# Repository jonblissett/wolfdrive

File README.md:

# wolfdrive
Motor drive inverter designed to be used with the Cree CAS325M12HM2 silicon carbide MOSFETs.

Anticipated specifications:
Peak power, 250kW
Current, ~300Arms
DC bus voltage, <800Vdc

## /controller

Control board, using STM32H743 microcontroller. Accepts analogue signals for throttle, will output FOC signals to gate drivers.

## /firmware

Software repository for controller - currently empty!

## /DCbus

PCB to connect DC bus capacitors with low stray inductance

## /DCsnubber

Alternative DC bus capacitor connection for small capacitors above devices like in early evaluation kit from Cree. May work out to be a cheaper option than /DCbus.

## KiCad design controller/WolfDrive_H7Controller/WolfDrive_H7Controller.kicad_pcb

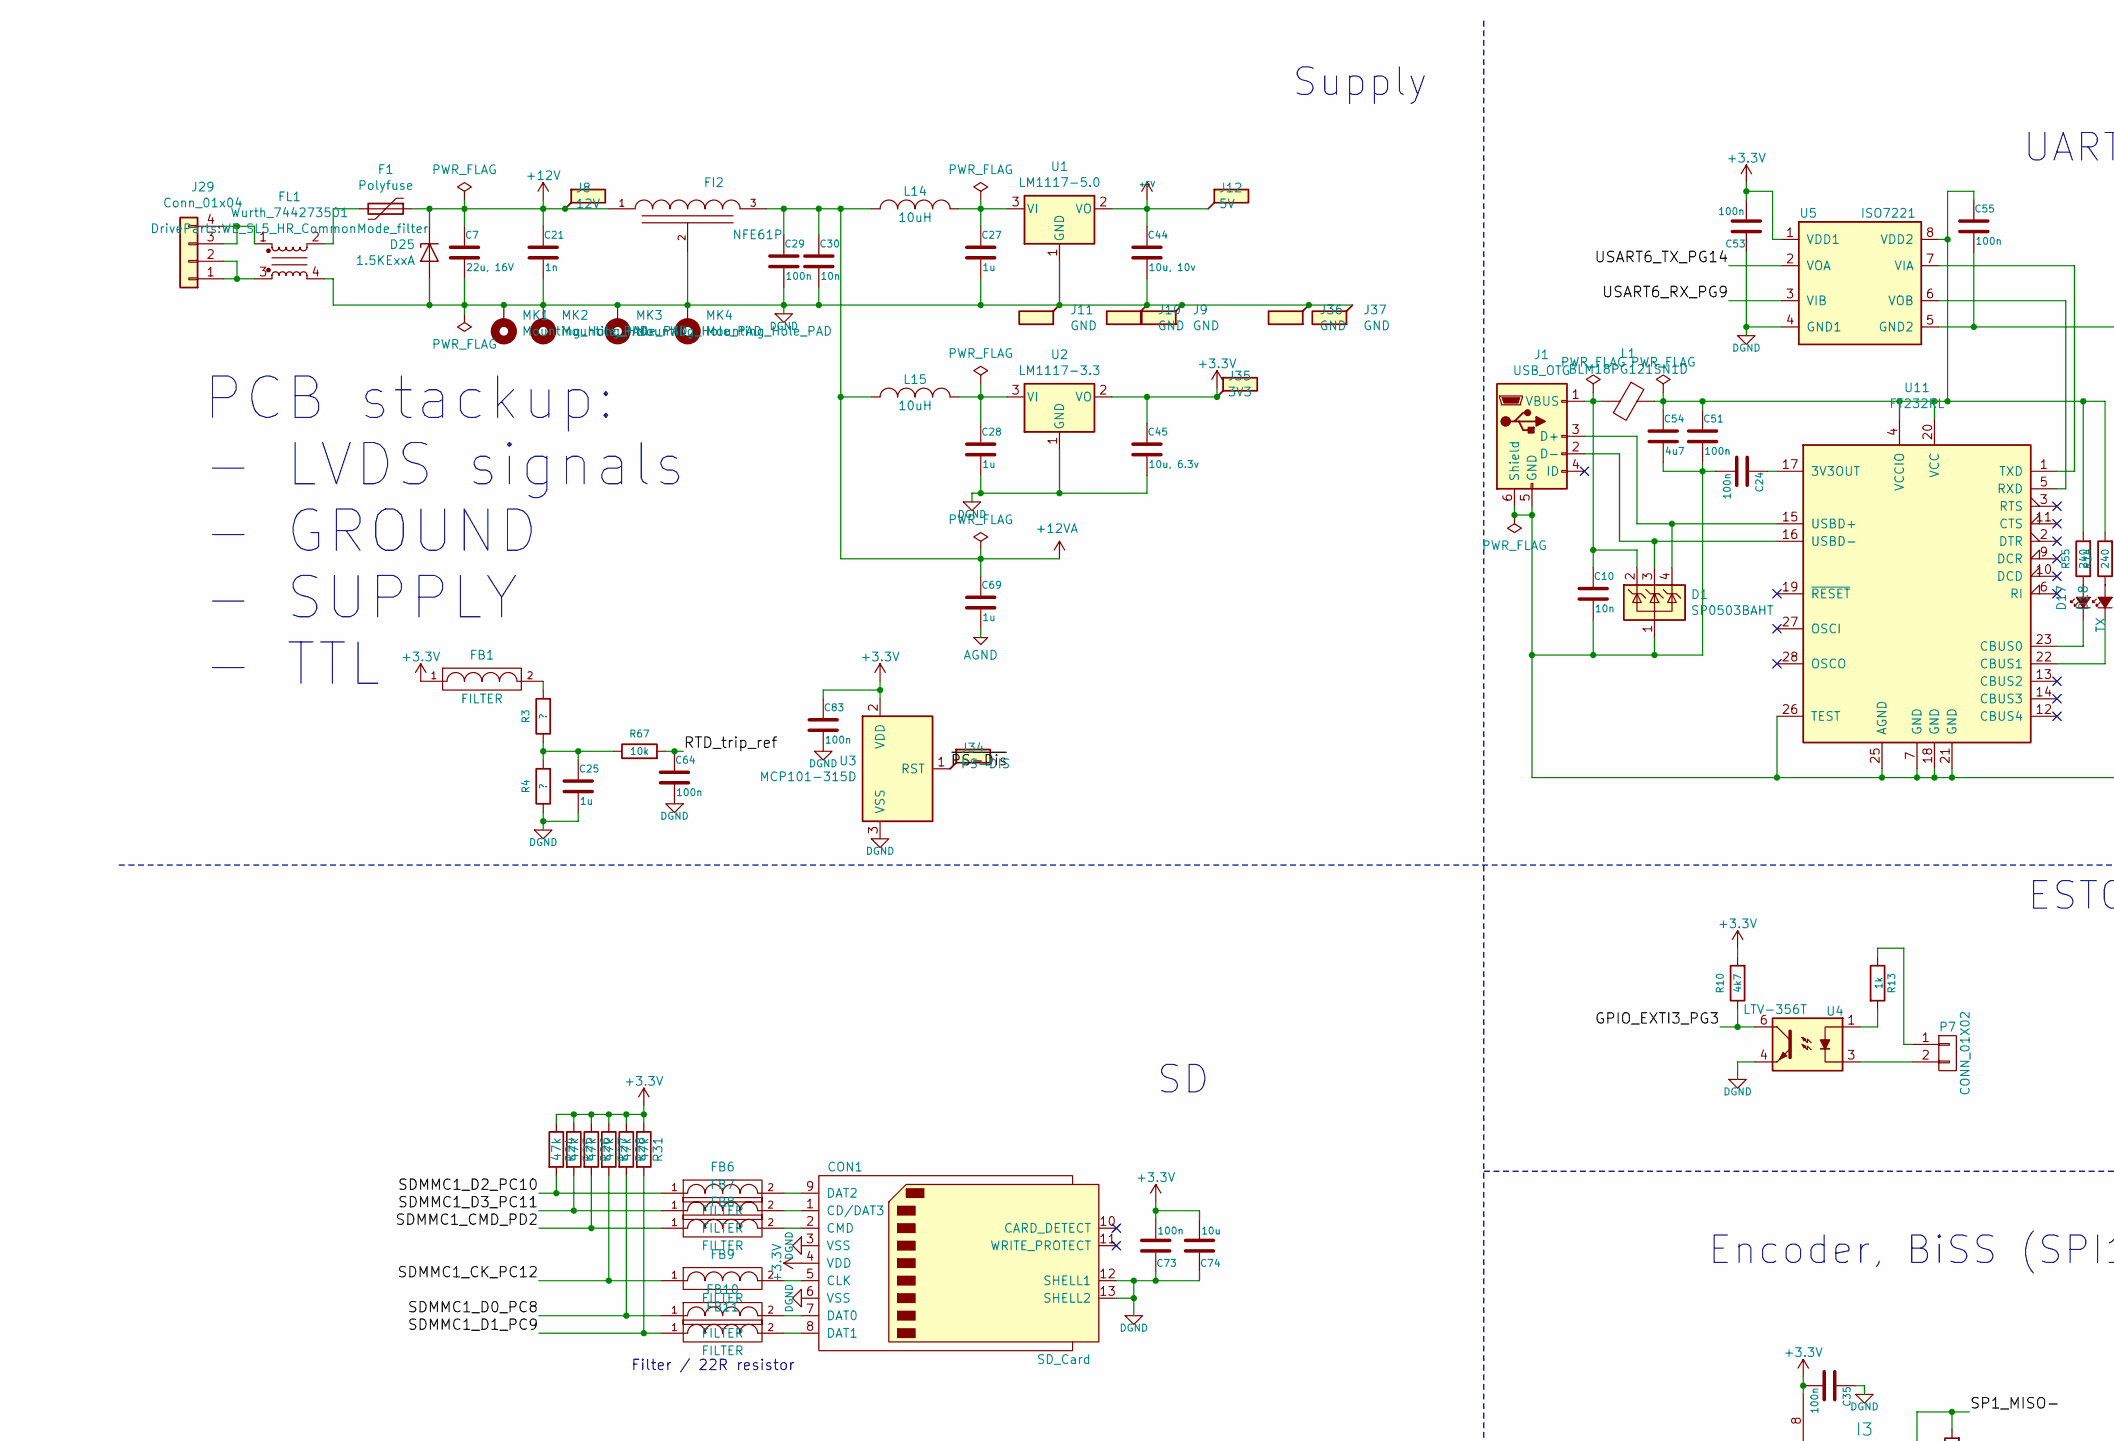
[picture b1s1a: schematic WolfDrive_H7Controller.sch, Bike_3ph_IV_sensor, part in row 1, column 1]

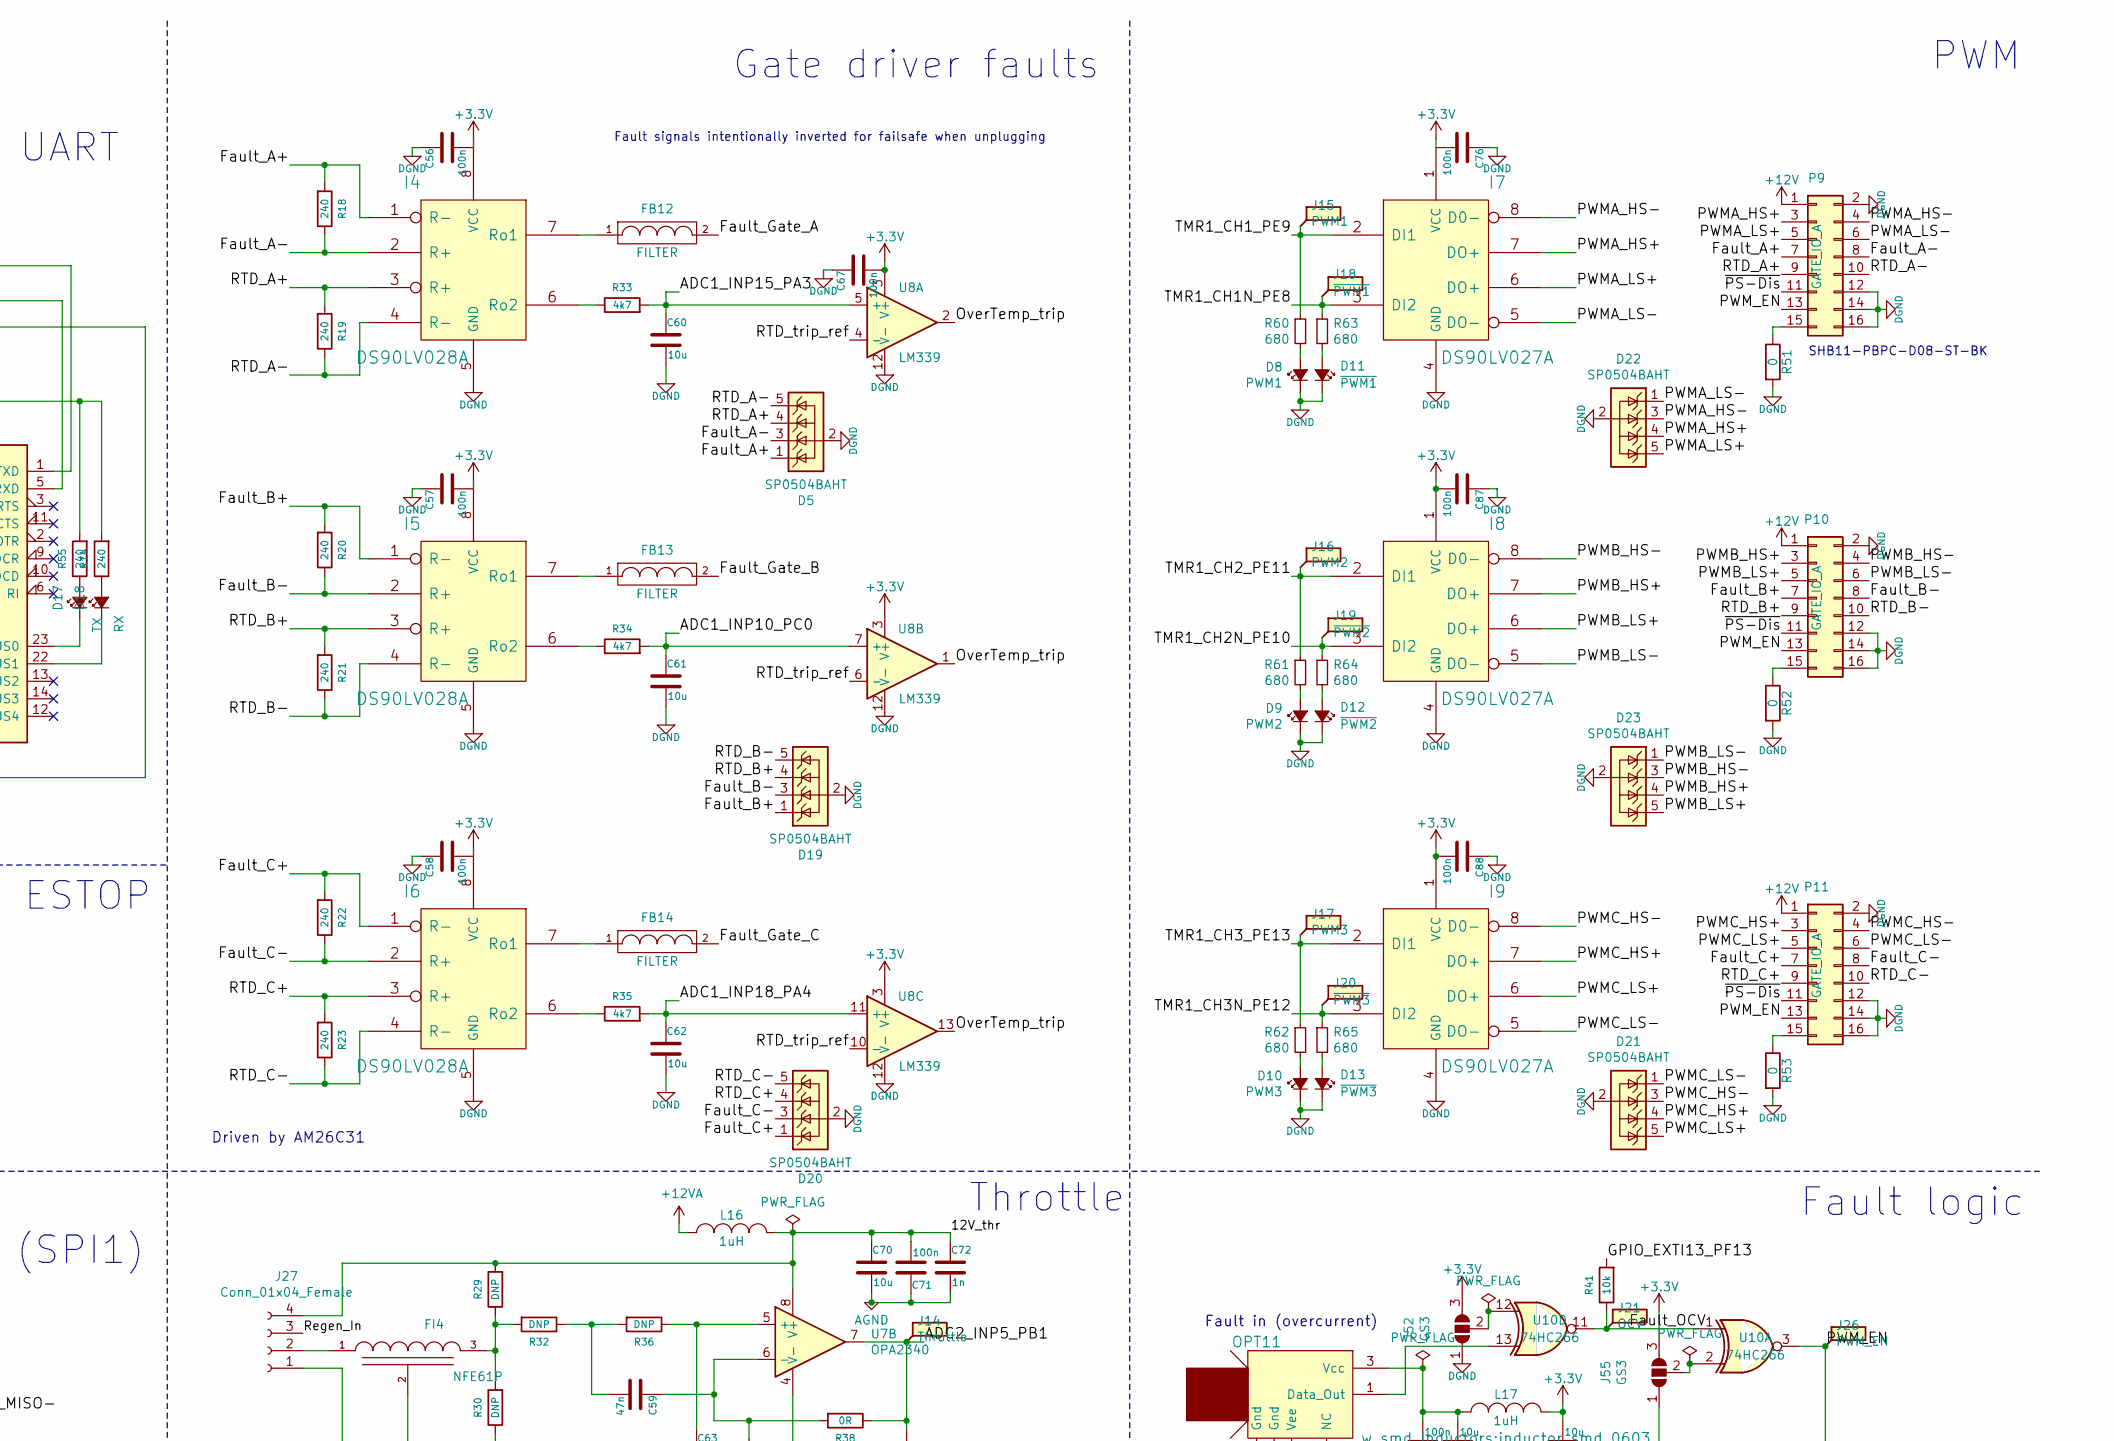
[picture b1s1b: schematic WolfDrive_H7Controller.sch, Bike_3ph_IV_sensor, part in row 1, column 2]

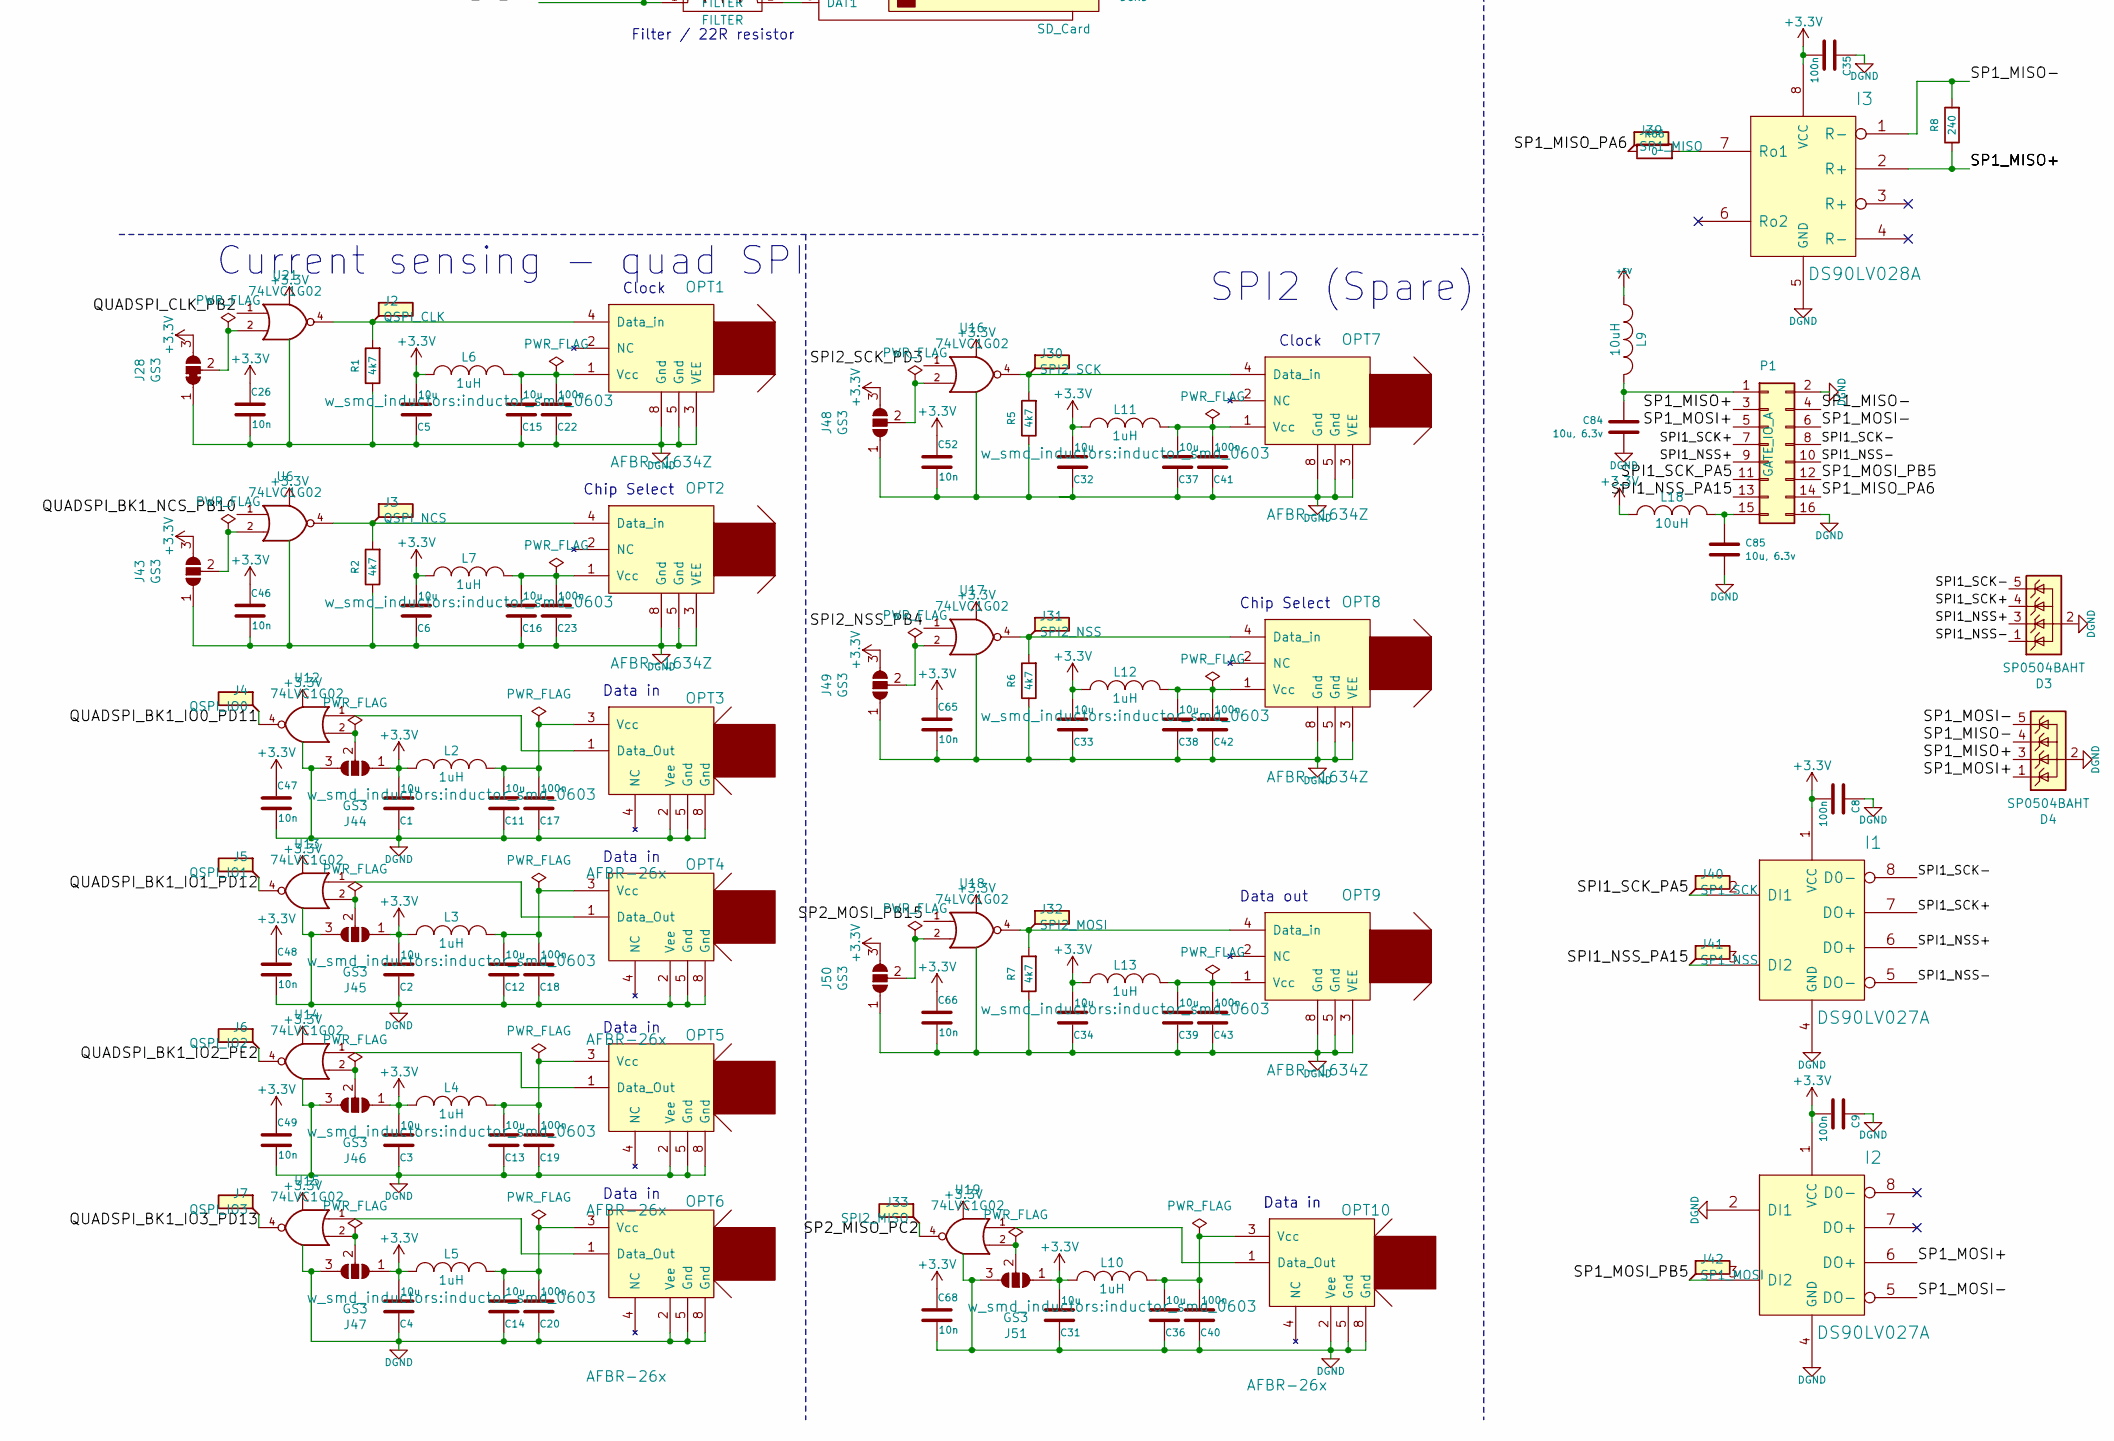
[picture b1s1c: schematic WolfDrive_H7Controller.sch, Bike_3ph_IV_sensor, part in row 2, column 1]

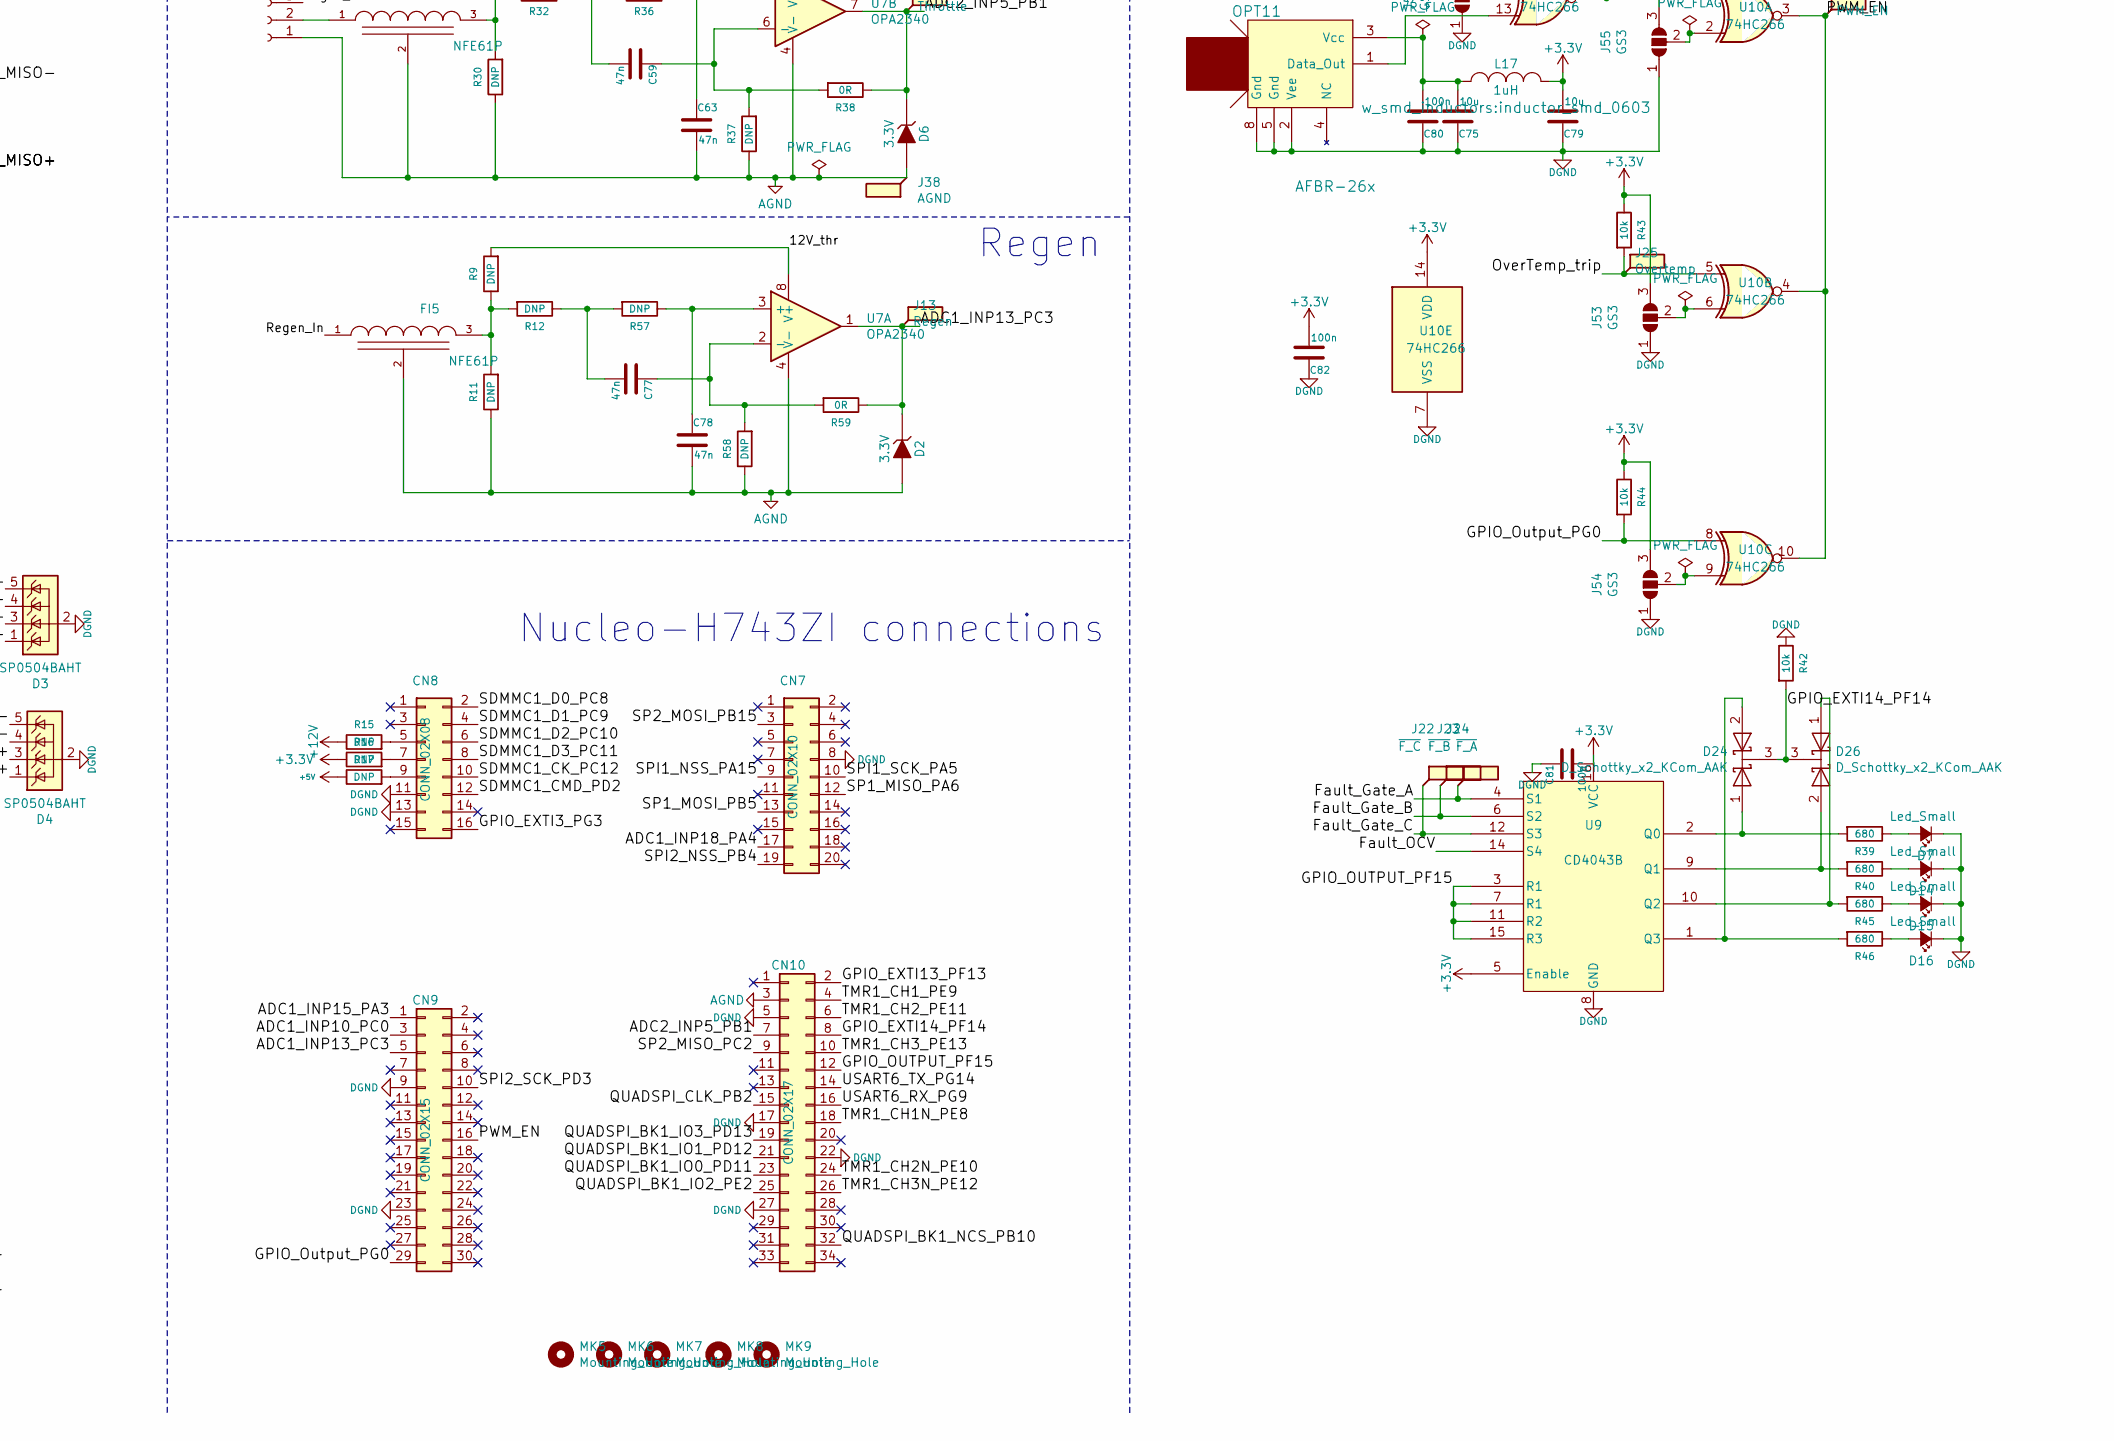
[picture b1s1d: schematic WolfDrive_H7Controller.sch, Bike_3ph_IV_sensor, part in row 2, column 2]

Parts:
C1, C2, C3, C4, C5, C6, C11, C12, C13, C14, C15, C16, C31, C32, C33, C34, C36, C37, C38, C39, C60, C61, C62, C70, C74, C75, C79: 10u; C_0805
C7: 22u, 16V; C_1210_HandSoldering
C8, C9, C17, C18, C19, C20, C22, C23, C24, C29, C35, C40, C41, C42, C43, C51, C53, C55, C56, C57, C58, C64, C67, C71, C73, C76, C80, C81, C82, C83, C87, C88: 100n; C_0603_HandSoldering
C10, C26, C30, C46, C47, C48, C49, C52, C65, C66, C68: 10n; C_0603_HandSoldering
C21, C72: 1n; C_0603_HandSoldering
C25, C27, C28, C69: 1u; C_0603_HandSoldering
C44: 10u, 10v; C_0805
C45, C84, C85: 10u, 6.3v; C_0805
C54: 4u7; C_0805
C59, C63, C77, C78: 47n; C_0603_HandSoldering
CN7: CONN_02X10; Socket_Strip_Straight_2x10_Pitch2.54mm
CN8: CONN_02X08; Socket_Strip_Straight_2x08_Pitch2.54mm
CN9: CONN_02X15; Socket_Strip_Straight_2x15_Pitch2.54mm
CN10: CONN_02X17; Socket_Strip_Straight_2x17_Pitch2.54mm
CON1: SD_Card; SD_Card_Receptacle
D1: SP0503BAHT; SOT-143R_Reverse_Handsoldering
D2, D6: 3.3V; D_SOD-523
D3, D4, D5, D19, D20, D21, D22, D23: SP0504BAHT; TSOT-23-5
D7, D14, D15, D16: Led_Small; LED_0603_HandSoldering
D8: PWM1; LED_0603_HandSoldering
D9: PWM2; LED_0603_HandSoldering
D10: PWM3; LED_0603_HandSoldering
D11: ~PWM1; LED_0603_HandSoldering
D12: ~PWM2; LED_0603_HandSoldering
D13: ~PWM3; LED_0603_HandSoldering
D17: TX; LED_0603_HandSoldering
D18: RX; LED_0603_HandSoldering
D24, D26: D_Schottky_x2_KCom_AAK; TSOT-23
D25: 1.5KExxA; D_SMB-SMC_Universal_Handsoldering
F1: Polyfuse; Fuse_1812_4532Metric_Pad1.24x3.50mm_HandSolder
FB1, FB6, FB7, FB8, FB9, FB10, FB11, FB12, FB13, FB14: FILTER; inductor_smd_0805
FI2, FI4, FI5: NFE61P; EMI_Filter_murata
FL1: Wurth_744273501; WE_SL5_HR_CommonMode_filter
I1, I2, I7, I8, I9: DS90LV027A; SOIC-8_3.9x4.9mm_Pitch1.27mm
I3, I4, I5, I6: DS90LV028A; SOIC-8_3.9x4.9mm_Pitch1.27mm
J1: USB_OTG; USB_Mini-B
J2: QSPI_CLK; Test_Point
J3: QSPI_NCS; Test_Point
J4: QSPI_IO0; Test_Point
J5: QSPI_IO1; Test_Point
J6: QSPI_IO2; Test_Point
J7: QSPI_IO3; Test_Point
J8: 12V; Test_Point
J9, J10, J11, J36, J37: GND; Test_Point
J12: 5V; Test_Point
J13: Regen; Test_Point
J14: Throttle; Test_Point
J15: PWM1; Test_Point
J16: PWM2; Test_Point
J17: PWM3; Test_Point
J18: ~PWM1; Test_Point
J19: ~PWM2; Test_Point
J20: ~PWM3; Test_Point
J21: OCV; Test_Point
J22: ~F_C; Test_Point
J23: ~F_B; Test_Point
J24: ~F_A; Test_Point
J25: Overtemp; Test_Point
J26: PWM_EN; Test_Point
J27: Conn_01x04_Female; TerminalBlock_Pheonix_PT-3.5mm_4pol
J28, J43, J44, J45, J46, J47, J48, J49, J50, J51, J52, J53, J54, J55: GS3
J29: Conn_01x04; PhoenixContact_MSTB-GF_04x5.08mm_Angled_ThreadedFlange_Moun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
J30: SPI2_SCK; Test_Point
J31: SPI2_NSS; Test_Point
J32: SPI2_MOSI; Test_Point
J33: SPI2_MISO; Test_Point
J34: PS-DIS; Test_Point
J35: 3V3; Test_Point
J38: AGND; Test_Point
J39: SP1_MISO; Test_Point
J40: SP1_SCK; Test_Point
J41: SP1_NSS; Test_Point
J42: SP1_MOSI; Test_Point
L1: BLM18PG121SN1D; inductor_smd_0603
L2, L3, L4, L5, L6, L7, L10, L11, L12, L13, L16, L17: 1uH; inductor_smd_0603
L9, L14, L15, L18: 10uH; Neosid_Inductor_SM-NE45_SMD1812
MK1, MK2, MK3, MK4: Mounting_Hole_PAD; MountingHole_4.3mm_M4_Pad_Via
MK5, MK6, MK7, MK8, MK9: Mounting_Hole; MountingHole_3.2mm_M3
OPT1, OPT2, OPT7, OPT8, OPT9: AFBR-1634Z; HFBR-xx2xZ
OPT3, OPT4, OPT5, OPT6, OPT10, OPT11: AFBR-26x; HFBR-xx2xZ
P1, P9, P10, P11: GATE_IO_A; IDC-Header_2x08_Pitch2.54mm_Straight
P7: CONN_01X02; TerminalBlock_Pheonix_PT-3.5mm_2pol
R1, R2, R5, R6, R7, R10, R33, R34, R35: 4k7; R_0603_HandSoldering
R3, R4: ?; R_0603_HandSoldering
R8, R14, R18, R19, R20, R21, R22, R23, R55: 240; R_0603_HandSoldering
R9, R11, R12, R15, R16, R17, R29, R30, R32, R36, R37, R57, R58: DNP; R_0603_HandSoldering
R13: 1k; R_0603_HandSoldering
R24, R25, R26, R27, R28, R31: 47k; R_0603_HandSoldering
R38, R59: 0R; R_0603_HandSoldering
R39, R40, R45, R46, R60, R61, R62, R63, R64, R65: 680; R_0603_HandSoldering
R41, R42, R43, R44, R67: 10k; R_0603_HandSoldering
R51, R52, R53, R66: 0; R_0603_HandSoldering
U1: LM1117-5.0; TO-263-3_TabPin2
U2: LM1117-3.3; TO-263-3_TabPin2
U3: MCP101-315D; SOT-23_Handsoldering
U4: LTV-356T; DIP-6_W7.62mm_SMD
U5: ISO7221; SOIC-8_3.9x4.9mm_Pitch1.27mm
U6, U12, U13, U14, U15, U16, U17, U18, U19, U21: 74LVC1G02; SOT-353_SC-70-5_Handsoldering
U7: OPA2340; SOIC-8_3.9x4.9mm_Pitch1.27mm
U8: LM339; SOIC-14_3.9x8.7mm_Pitch1.27mm
U9: CD4043B; SOIC-16_3.9x9.9mm_Pitch1.27mm
U10: 74HC266; SOIC-14_3.9x8.7mm_Pitch1.27mm
U11: FT232RL; SSOP-28_5.3x10.2mm_Pitch0.65mm

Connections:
+3V3: C1.2, C2.2, C3.2, C4.2, C5.2, C6.2, C8.2, C9.2, C26.1, C31.2, C32.2, C33.2, C34.2, C35.2, C45.1, C46.1, C47.1, C48.1, C49.1, C52.1, C53.2, C56.2, C57.2, C58.2, C65.1, C66.1, C67.2, C68.1, C73.2, C74.2, C76.2, C79.2, C81.2, C82.2, C83.1, C87.2, C88.2, CON1.4 (VDD), FB1.1, I1.1 (VCC), I2.1 (VCC), I3.8 (VCC), I4.8 (VCC), I5.8 (VCC), I6.8 (VCC), I7.1 (VCC), I8.1 (VCC), I9.1 (VCC), J28.3 (B), J35.1, J43.3 (B), J44.1 (A), J45.1 (A), J46.1 (A), J47.1 (A), J48.3 (B), J49.3 (B), J50.3 (B), J51.1 (A), J52.3 (B), J53.3 (B), J54.3 (B), J55.3 (B), L2.2, L3.2, L4.2, L5.2, L6.2, L7.2, L10.2, L11.2, L12.2, L13.2, L17.1, L18.2, R10.2, R16.1, R24.1, R25.1, R26.1, R27.1, R28.1, R31.1, R43.1, R44.1, U2.2 (VO), U3.2 (VDD), U5.1 (VDD1), U6.5 (VCC), U8.3 (V+), U9.5 (Enable), U9.16 (VCC), U10.14 (VDD), U12.5 (VCC), U13.5 (VCC), U14.5 (VCC), U15.5 (VCC), U16.5 (VCC), U17.5 (VCC), U18.5 (VCC), U19.5 (VCC), U21.5 (VCC)
+5V: C44.1, J12.1, L9.1, R17.1, U1.2 (VO)
+12V: C7.1, C21.1, D25.1 (A1), F1.1, FI2.1 (VI), J8.1, P9.1, P10.1, P11.1, R15.1
+12VA: C29.1, C30.1, C69.1, FI2.3 (VO), L14.1, L15.1, L16.2
/12V_thr: C70.1, C71.2, C72.1, J27.4, L16.1, R9.2, R29.2, U7.8 (V+)
/ADC1_INP10_PC0: C61.1, CN9.3, R34.2, U8.7 (+)
/ADC1_INP13_PC3: CN9.5, D2.1 (K), J13.1, R59.1, U7.1
/ADC1_INP15_PA3: C60.1, CN9.1, R33.2, U8.5 (+)
/ADC1_INP18_PA4: C62.1, CN7.17, R35.2, U8.11 (+)
/ADC2_INP5_PB1: CN10.7, D6.1 (K), J14.1, R38.1, U7.7
/Fault_A+: D5.1 (K), I4.1 (R-), P9.7, R18.2
/Fault_A-: D5.3 (K), I4.2 (R+), P9.8, R18.1
/Fault_B+: D19.1 (K), I5.1 (R-), P10.7, R20.2
/Fault_B-: D19.3 (K), I5.2 (R+), P10.8, R20.1
/Fault_C+: D20.1 (K), I6.1 (R-), P11.7, R22.2
/Fault_C-: D20.3 (K), I6.2 (R+), P11.8, R22.1
/Fault_Gate_A: FB12.2, J24.1, U9.4 (S1)
/Fault_Gate_B: FB13.2, J23.1, U9.6 (S2)
/Fault_Gate_C: FB14.2, J22.1, U9.12 (S3)
/Fault_OCV: J21.1, R41.1, U9.14 (S4), U10.1, U10.11
/GPIO_EXTI3_PG3: CN8.16, R10.1, U4.6
/GPIO_EXTI13_PF13: CN10.2, R41.2
/GPIO_EXTI14_PF14: CN10.8, D24.3 (K), D26.3 (K), R42.2
/GPIO_OUTPUT_PF15: CN10.12, U9.3 (R1), U9.7 (R1), U9.11 (R2), U9.15 (R3)
/GPIO_Output_PG0: CN9.29, R44.2, U10.8
/OverTemp_trip: J25.1, R43.2, U8.1, U8.2, U8.13, U10.5
/PWMA_HS+: D22.4 (K), I7.7 (DO+), P9.3
/PWMA_HS-: D22.3 (K), I7.8 (D0-), P9.4
/PWMA_LS+: D22.5 (K), I7.6 (DO+), P9.5
/PWMA_LS-: D22.1 (K), I7.5 (DO-), P9.6
/PWMB_HS+: D23.4 (K), I8.7 (DO+), P10.3
/PWMB_HS-: D23.3 (K), I8.8 (D0-), P10.4
/PWMB_LS+: D23.5 (K), I8.6 (DO+), P10.5
/PWMB_LS-: D23.1 (K), I8.5 (DO-), P10.6
/PWMC_HS+: D21.4 (K), I9.7 (DO+), P11.3
/PWMC_HS-: D21.3 (K), I9.8 (D0-), P11.4
/PWMC_LS+: D21.5 (K), I9.6 (DO+), P11.5
/PWMC_LS-: D21.1 (K), I9.5 (DO-), P11.6
/PWM_EN: CN9.16, J26.1, P9.13, P10.13, P11.13, U10.3, U10.4, U10.10
/QUADSPI_BK1_IO0_PD11: CN10.23, J4.1, U12.4
/QUADSPI_BK1_IO1_PD12: CN10.21, J5.1, U13.4
/QUADSPI_BK1_IO2_PE2: CN10.25, J6.1, U14.4
/QUADSPI_BK1_IO3_PD13: CN10.19, J7.1, U15.4
/QUADSPI_BK1_NCS_PB10: CN10.32, U6.1
/QUADSPI_CLK_PB2: CN10.15, U21.1
/RTD_A+: D5.4 (K), I4.3 (R+), P9.9, R19.2
/RTD_A-: D5.5 (K), I4.4 (R-), P9.10, R19.1
/RTD_B+: D19.4 (K), I5.3 (R+), P10.9, R21.2
/RTD_B-: D19.5 (K), I5.4 (R-), P10.10, R21.1
/RTD_C+: D20.4 (K), I6.3 (R+), P11.9, R23.2
/RTD_C-: D20.5 (K), I6.4 (R-), P11.10, R23.1
/RTD_trip_ref: C64.1, R67.2, U8.4 (-), U8.6 (-), U8.10 (-)
/Regen_In: FI5.1 (VI), J27.3
/SDMMC1_CK_PC12: CN8.10, FB9.1, R27.2
/SDMMC1_CMD_PD2: CN8.12, FB8.1, R26.2
/SDMMC1_D0_PC8: CN8.2, FB10.1, R28.2
/SDMMC1_D1_PC9: CN8.4, FB11.1, R31.2
/SDMMC1_D2_PC10: CN8.6, FB6.1, R24.2
/SDMMC1_D3_PC11: CN8.8, FB7.1, R25.2
/SP1_MISO+: D4.3 (K), I3.2 (R+), P1.3, R8.1
/SP1_MISO-: D4.4 (K), I3.1 (R-), P1.4, R8.2
/SP1_MISO_PA6: CN7.12, J39.1, P1.14, R66.1
/SP1_MOSI+: D4.1 (K), I2.6 (DO+), P1.5
/SP1_MOSI-: D4.5 (K), I2.5 (DO-), P1.6
/SP1_MOSI_PB5: CN7.13, I2.3 (DI2), J42.1, P1.12
/SP2_MISO_PC2: CN10.9, J33.1, U19.4
/SP2_MOSI_PB15: CN7.3, U18.1
/SPI1_NSS+: D3.3 (K), I1.6 (DO+), P1.9
/SPI1_NSS-: D3.1 (K), I1.5 (DO-), P1.10
/SPI1_NSS_PA15: CN7.9, I1.3 (DI2), J41.1, P1.13
/SPI1_SCK+: D3.4 (K), I1.7 (DO+), P1.7
/SPI1_SCK-: D3.5 (K), I1.8 (D0-), P1.8
/SPI1_SCK_PA5: CN7.10, I1.2 (DI1), J40.1, P1.11
/SPI2_NSS_PB4: CN7.19, U17.1
/SPI2_SCK_PD3: CN9.10, U16.1
/TMR1_CH1N_PE8: CN10.18, I7.3 (DI2), J18.1, R63.1
/TMR1_CH1_PE9: CN10.4, I7.2 (DI1), J15.1, R60.1
/TMR1_CH2N_PE10: CN10.24, I8.3 (DI2), J19.1, R64.1
/TMR1_CH2_PE11: CN10.6, I8.2 (DI1), J16.1, R61.1
/TMR1_CH3N_PE12: CN10.26, I9.3 (DI2), J20.1, R65.1
/TMR1_CH3_PE13: CN10.10, I9.2 (DI1), J17.1, R62.1
/USART6_RX_PG9: CN10.16, U5.3 (VIB)
/USART6_TX_PG14: CN10.14, U5.2 (VOA)
/~PS-Dis: J34.1, P9.11, P10.11, P11.11, U3.1 (RST)
AGND: C63.2, C69.2, C70.2, C71.1, C72.2, C78.2, CN10.3, D2.2 (A), D6.2 (A), FI4.2 (GND), FI5.2 (GND), J27.1, J38.1, R11.1, R30.1, R37.1, R58.1, U7.4 (V-)
DGND: C1.1, C2.1, C3.1, C4.1, C5.1, C6.1, C7.2, C8.1, C9.1, C11.1, C12.1, C13.1, C14.1, C15.1, C16.1, C17.1, C18.1, C19.1, C20.1, C21.2, C22.1, C23.1, C25.2, C26.2, C27.2, C28.2, C29.2, C30.2, C31.1, C32.1, C33.1, C34.1, C35.1, C36.1, C37.1, C38.1, C39.1, C40.1, C41.1, C42.1, C43.1, C44.2, C45.2, C46.2, C47.2, C48.2, C49.2, C52.2, C53.1, C56.1, C57.1, C58.1, C60.2, C61.2, C62.2, C64.2, C65.2, C66.2, C67.1, C68.2, C73.1, C74.1, C75.1, C76.1, C79.1, C80.1, C81.1, C82.1, C83.2, C84.2, C85.2, C87.1, C88.1, CN7.8, CN8.11, CN8.13, CN9.9, CN9.23, CN10.5, CN10.17, CN10.22, CN10.27, CON1.3 (VSS), CON1.6 (VSS), CON1.12 (SHELL1), CON1.13 (SHELL2), D3.2 (A), D4.2 (A), D5.2 (A), D7.1 (K), D8.1 (K), D9.1 (K), D10.1 (K), D11.1 (K), D12.1 (K), D13.1 (K), D14.1 (K), D15.1 (K), D16.1 (K), D19.2 (A), D20.2 (A), D21.2 (A), D22.2 (A), D23.2 (A), D25.2 (A2), FI2.2 (GND), FL1.4, I1.4 (GND), I2.2 (DI1), I2.4 (GND), I3.5 (GND), I4.5 (GND), I5.5 (GND), I6.5 (GND), I7.4 (GND), I8.4 (GND), I9.4 (GND), J9.1, J10.1, J11.1, J28.1 (A), J36.1, J37.1, J43.1 (A), J44.3 (B), J45.3 (B), J46.3 (B), J47.3 (B), J48.1 (A), J49.1 (A), J50.1 (A), J51.3 (B), J52.1 (A), J53.1 (A), J54.1 (A), J55.1 (A), MK1.1, MK2.1, MK3.1, MK4.1, OPT1.3 (VEE), OPT1.5 (Gnd), OPT1.8 (Gnd), OPT2.3 (VEE), OPT2.5 (Gnd), OPT2.8 (Gnd), OPT3.2 (Vee), OPT3.5 (Gnd), OPT3.8 (Gnd), OPT4.2 (Vee), OPT4.5 (Gnd), OPT4.8 (Gnd), OPT5.2 (Vee), OPT5.5 (Gnd), OPT5.8 (Gnd), OPT6.2 (Vee), OPT6.5 (Gnd), OPT6.8 (Gnd), OPT7.3 (VEE), OPT7.5 (Gnd), OPT7.8 (Gnd), OPT8.3 (VEE), OPT8.5 (Gnd), OPT8.8 (Gnd), OPT9.3 (VEE), OPT9.5 (Gnd), OPT9.8 (Gnd), OPT10.2 (Vee), OPT10.5 (Gnd), OPT10.8 (Gnd), OPT11.2 (Vee), OPT11.5 (Gnd), OPT11.8 (Gnd), P1.2, P1.16, P9.2, P9.12, P9.14, P9.16, P10.2, P10.12, P10.14, P10.16, P11.2, P11.12, P11.14, P11.16, R1.1, R2.1, R4.1, R5.1, R6.1, R7.1, R42.1, R51.2, R52.2, R53.2, U1.1 (GND), U2.1 (GND), U3.3 (VSS), U4.4, U5.4 (GND1), U6.3 (GND), U8.12 (V-), U9.8 (GND), U10.7 (VSS), U12.3 (GND), U13.3 (GND), U14.3 (GND), U15.3 (GND)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
unnamed: C10.1, D1.2 (K), J1.1 (VBUS), L1.2
unnamed: C10.2, C24.2, C51.2, C54.2, C55.2, D1.1 (A), J1.5 (GND), J1.6 (Shield), U5.5 (GND2), U11.7 (GND), U11.18 (GND), U11.21 (GND), U11.25 (AGND), U11.26 (TEST)
unnamed: C11.2, C17.2, L2.1, OPT3.3 (Vcc)
unnamed: C12.2, C18.2, L3.1, OPT4.3 (Vcc)
unnamed: C13.2, C19.2, L4.1, OPT5.3 (Vcc)
unnamed: C14.2, C20.2, L5.1, OPT6.3 (Vcc)
unnamed: C15.2, C22.2, L6.1, OPT1.1 (Vcc)
unnamed: C16.2, C23.2, L7.1, OPT2.1 (Vcc)
unnamed: C24.1, U11.17 (3V3OUT)
unnamed: C25.1, R3.1, R4.2, R67.1
unnamed: C27.1, L14.2, U1.3 (VI)
unnamed: C28.1, L15.2, U2.3 (VI)
unnamed: C36.2, C40.2, L10.1, OPT10.3 (Vcc)
unnamed: C37.2, C41.2, L11.1, OPT7.1 (Vcc)
unnamed: C38.2, C42.2, L12.1, OPT8.1 (Vcc)
unnamed: C39.2, C43.2, L13.1, OPT9.1 (Vcc)
unnamed: C51.1, C54.1, C55.1, L1.1, R14.2, R55.2, U5.8 (VDD2), U11.4 (VCCIO), U11.20 (VCC)
unnamed: C59.1, R37.2, R38.2, U7.6 (-)
unnamed: C59.2, R32.1, R36.2
unnamed: C63.1, R36.1, U7.5 (+)
unnamed: C75.2, C80.2, L17.2, OPT11.3 (Vcc)
unnamed: C77.1, R58.2, R59.2, U7.2 (-)
unnamed: C77.2, R12.1, R57.2
unnamed: C78.1, R57.1, U7.3 (+)
unnamed: C84.1, L9.2, P1.1
unnamed: C85.1, L18.1, P1.15
unnamed: CN8.5, R15.2
unnamed: CN8.7, R16.2
unnamed: CN8.9, R17.2
unnamed: CON1.1 (CD/DAT3), FB7.2
unnamed: CON1.2 (CMD), FB8.2
unnamed: CON1.5 (CLK), FB9.2
unnamed: CON1.7 (DAT0), FB10.2
unnamed: CON1.8 (DAT1), FB11.2
unnamed: CON1.9 (DAT2), FB6.2
unnamed: D1.3 (K), J1.2 (D-), U11.16 (USBD-)
unnamed: D1.4 (K), J1.3 (D+), U11.15 (USBD+)
unnamed: D7.2 (A), R39.1
unnamed: D8.2 (A), R60.2
unnamed: D9.2 (A), R61.2
unnamed: D10.2 (A), R62.2
unnamed: D11.2 (A), R63.2
unnamed: D12.2 (A), R64.2
unnamed: D13.2 (A), R65.2
unnamed: D14.2 (A), R40.1
unnamed: D15.2 (A), R45.1
unnamed: D16.2 (A), R46.1
unnamed: D17.1 (K), U11.23 (CBUS0)
unnamed: D17.2 (A), R55.1
unnamed: D18.1 (K), U11.22 (CBUS1)
unnamed: D18.2 (A), R14.1
unnamed: D24.1 (A), R39.2, U9.2 (Q0)
unnamed: D24.2 (A), R46.2, U9.1 (Q3)
unnamed: D26.1 (A), R45.2, U9.10 (Q2)
unnamed: D26.2 (A), R40.2, U9.9 (Q1)
unnamed: F1.2, FL1.2
unnamed: FB1.2, R3.2
unnamed: FB12.1, I4.7 (Ro1)
unnamed: FB13.1, I5.7 (Ro1)
unnamed: FB14.1, I6.7 (Ro1)
unnamed: FI4.1 (VI), J27.2
unnamed: FI4.3 (VO), R29.1, R30.2, R32.2
unnamed: FI5.3 (VO), R9.1, R11.2, R12.2
unnamed: FL1.1, J29.3, J29.4
unnamed: FL1.3, J29.1, J29.2
unnamed: I3.7 (Ro1), R66.2
unnamed: I4.6 (Ro2), R33.1
unnamed: I5.6 (Ro2), R34.1
unnamed: I6.6 (Ro2), R35.1
unnamed: J2.1, OPT1.4 (Data_in), R1.2, U21.4
unnamed: J3.1, OPT2.4 (Data_in), R2.2, U6.4
unnamed: J28.2 (C), U21.2
unnamed: J30.1, OPT7.4 (Data_in), R5.2, U16.4
unnamed: J31.1, OPT8.4 (Data_in), R6.2, U17.4
unnamed: J32.1, OPT9.4 (Data_in), R7.2, U18.4
unnamed: J43.2 (C), U6.2
unnamed: J44.2 (C), U12.2
unnamed: J45.2 (C), U13.2
unnamed: J46.2 (C), U14.2
unnamed: J47.2 (C), U15.2
unnamed: J48.2 (C), U16.2
unnamed: J49.2 (C), U17.2
unnamed: J50.2 (C), U18.2
unnamed: J51.2 (C), U19.2
unnamed: J52.2 (C), U10.12
unnamed: J53.2 (C), U10.6
unnamed: J54.2 (C), U10.9
unnamed: J55.2 (C), U10.2
unnamed: OPT3.1 (Data_Out), U12.1
unnamed: OPT4.1 (Data_Out), U13.1
unnamed: OPT5.1 (Data_Out), U14.1
unnamed: OPT6.1 (Data_Out), U15.1
unnamed: OPT10.1 (Data_Out), U19.1
unnamed: OPT11.1 (Data_Out), U10.13
unnamed: P7.1, R13.1
unnamed: P7.2, U4.3
unnamed: P9.15, R51.1
unnamed: P10.15, R52.1
unnamed: P11.15, R53.1
unnamed: R13.2, U4.1
unnamed: U5.7 (VIA), U11.1 (TXD)
unnamed: U5.6 (VOB), U11.5 (RXD)

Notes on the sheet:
Fault in (overcurrent)
UART
Throttle
Chip Select
Clock
Data in
Data out
PCB stackup: - LVDS signals - GROUND - SUPPLY - TTL
Current sensing - quad SPI
SPI2 (Spare)
Filter / 22R resistor
Encoder, BiSS (SPI1)
ESTOP
Fault logic
PWM
Gate driver faults
Supply
Nucleo-H743ZI connections
Driven by AM26C31
Regen
SHB11-PBPC-D08-ST-BK
Fault signals intentionally inverted for failsafe when unplugging

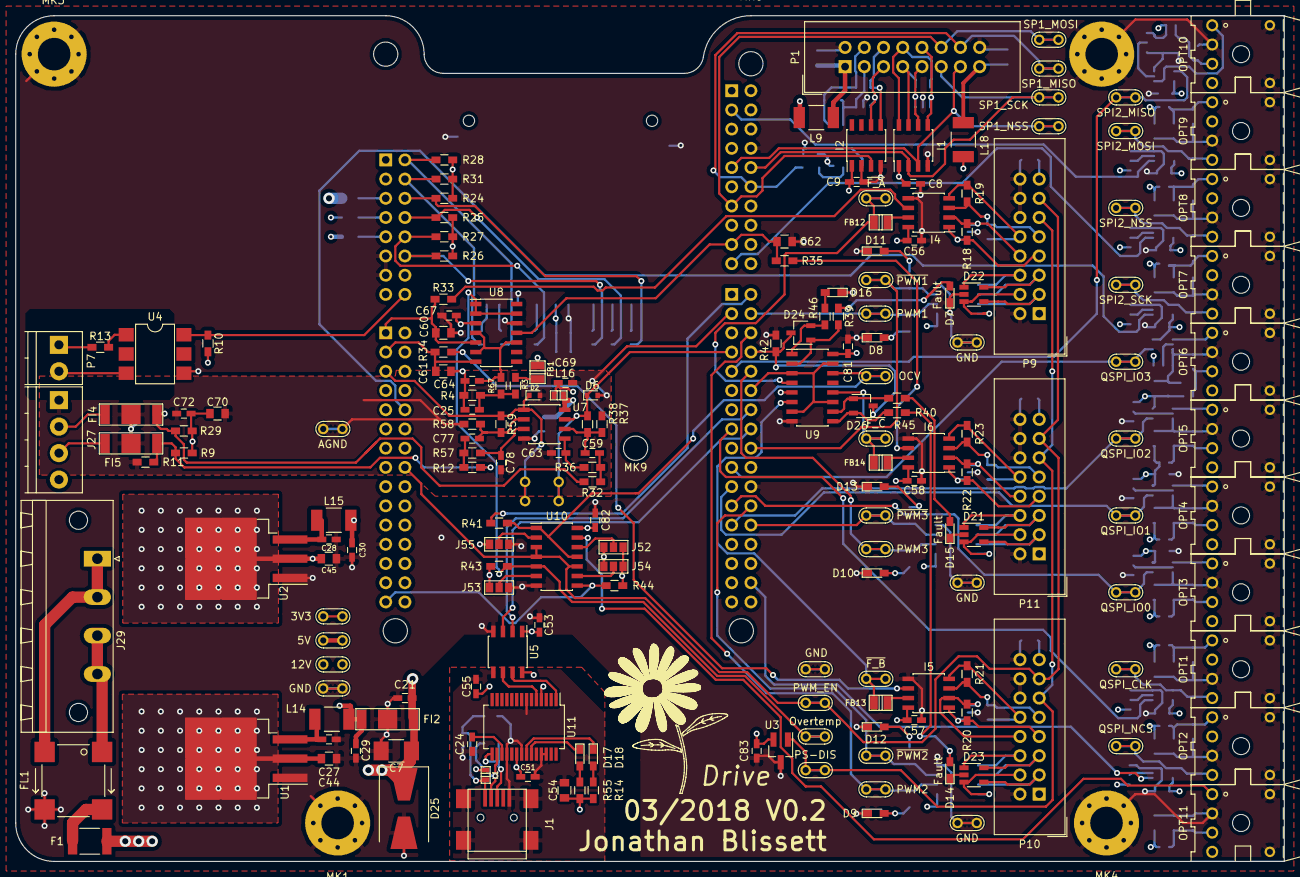
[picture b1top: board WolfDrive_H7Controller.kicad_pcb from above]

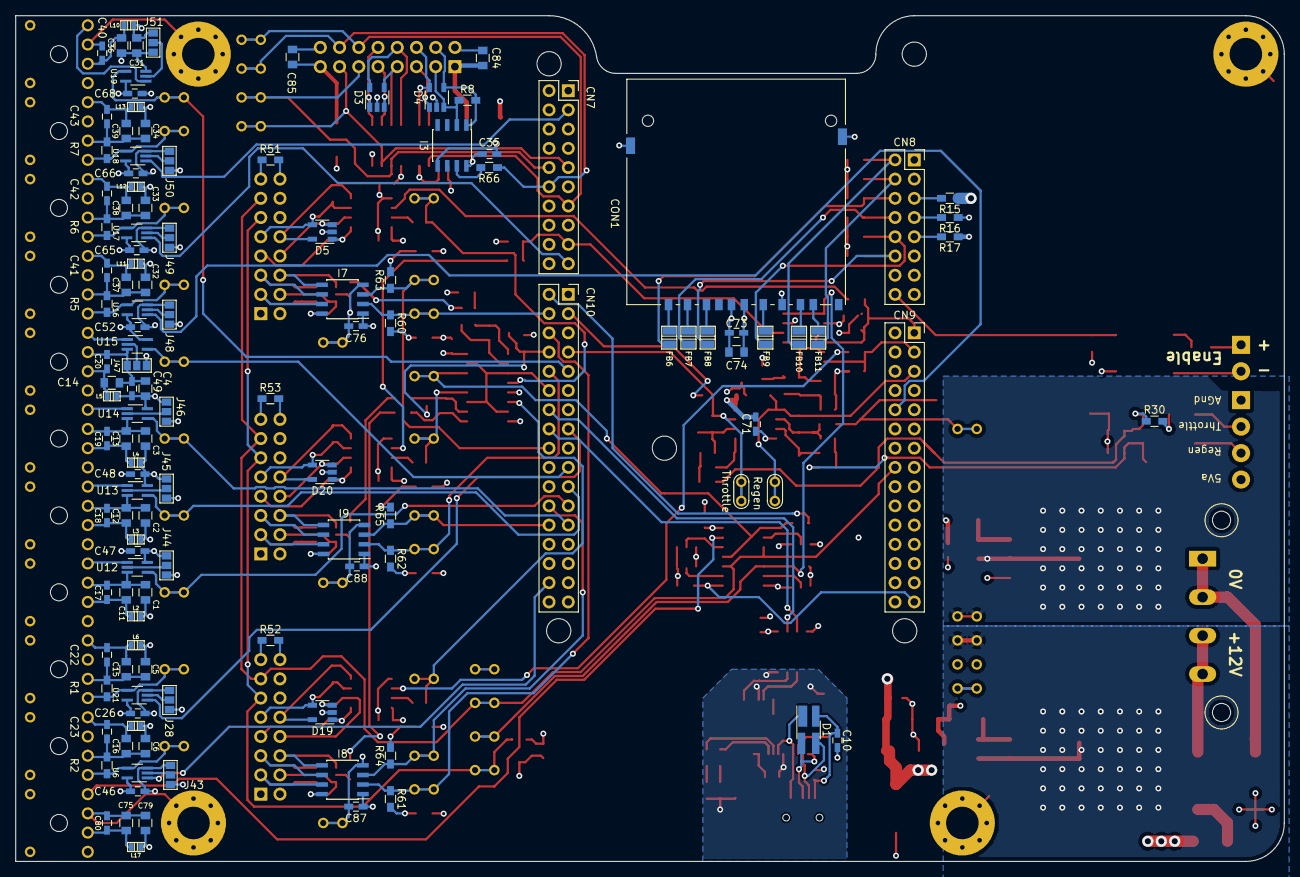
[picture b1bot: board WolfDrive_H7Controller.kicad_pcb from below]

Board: 4 copper layers, 167.6 x 111.8 mm, 319 parts (126 on the bottom side), 188 nets.
